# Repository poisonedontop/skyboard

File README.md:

# SkyBoard
I have been playing Hypixel Skyblock for a while now and while it's great, having keybinds to commands makes basically everything much more efficient. The problem with my normal keyboard is that it's too cluttered to set all command keybinds there as it will overlap with other keybinds.
That's why I'm creating this deck, to make a clean and efficient way to play the game. I haven't had much prior experience with electronics, so I think this will be a great first project! <br/>
Screenshot of the full case: <br/>
 <br/>

Screenshot of the schematic: <br/>

<br/>
Screenshot of the PCB:<br/>

BOM: <br/>
1x Seeed XIAO RP2040 <br/>
6x MX-Style switches <br/>
1x EC11 Rotary encoder <br/>
4x SK6812 MINI-E LEDs <br/>
3D printed case

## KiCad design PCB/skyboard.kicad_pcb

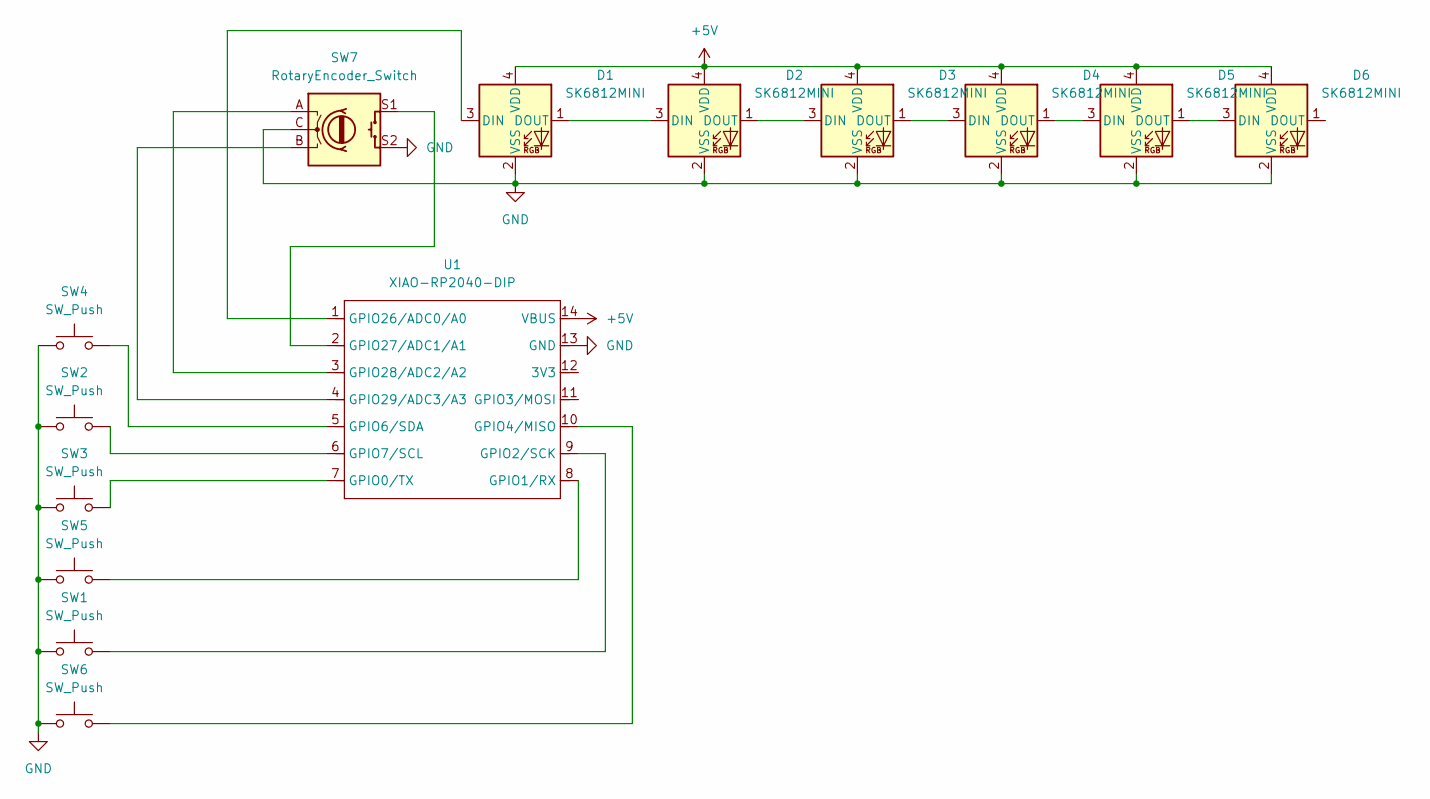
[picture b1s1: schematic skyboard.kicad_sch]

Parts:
D1, D2, D3, D4, D5, D6: SK6812MINI; MX_SK6812MINI-E_REV
SW1, SW2, SW3, SW4, SW5, SW6: SW_Push; SW_Cherry_MX_1.00u_PCB
SW7: RotaryEncoder_Switch; RotaryEncoder_Alps_EC11E-Switch_Vertical_H20mm
U1: XIAO-RP2040-DIP

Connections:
+5V: D1.4 (VDD), D2.4 (VDD), D3.4 (VDD), D4.4 (VDD), D5.4 (VDD), D6.4 (VDD), U1.14 (VBUS)
GND: D1.2 (VSS), D2.2 (VSS), D3.2 (VSS), D4.2 (VSS), D5.2 (VSS), D6.2 (VSS), SW1.1, SW2.1, SW3.1, SW4.1, SW5.1, SW6.1, SW7.C, SW7.S2, U1.13 (GND)
unnamed: D1.3 (DIN), U1.1 (GPIO26/ADC0/A0)
unnamed: D1.1 (DOUT), D2.3 (DIN)
unnamed: D2.1 (DOUT), D3.3 (DIN)
unnamed: D3.1 (DOUT), D4.3 (DIN)
unnamed: D4.1 (DOUT), D5.3 (DIN)
unnamed: D5.1 (DOUT), D6.3 (DIN)
unnamed: SW3.2, U1.7 (GPIO0/TX)
unnamed: SW5.2, U1.8 (GPIO1/RX)
unnamed: SW1.2, U1.9 (GPIO2/SCK)
unnamed: SW6.2, U1.10 (GPIO4/MISO)
unnamed: SW4.2, U1.5 (GPIO6/SDA)
unnamed: SW2.2, U1.6 (GPIO7/SCL)
unnamed: SW7.S1, U1.2 (GPIO27/ADC1/A1)
unnamed: SW7.A, U1.3 (GPIO28/ADC2/A2)
unnamed: SW7.B, U1.4 (GPIO29/ADC3/A3)

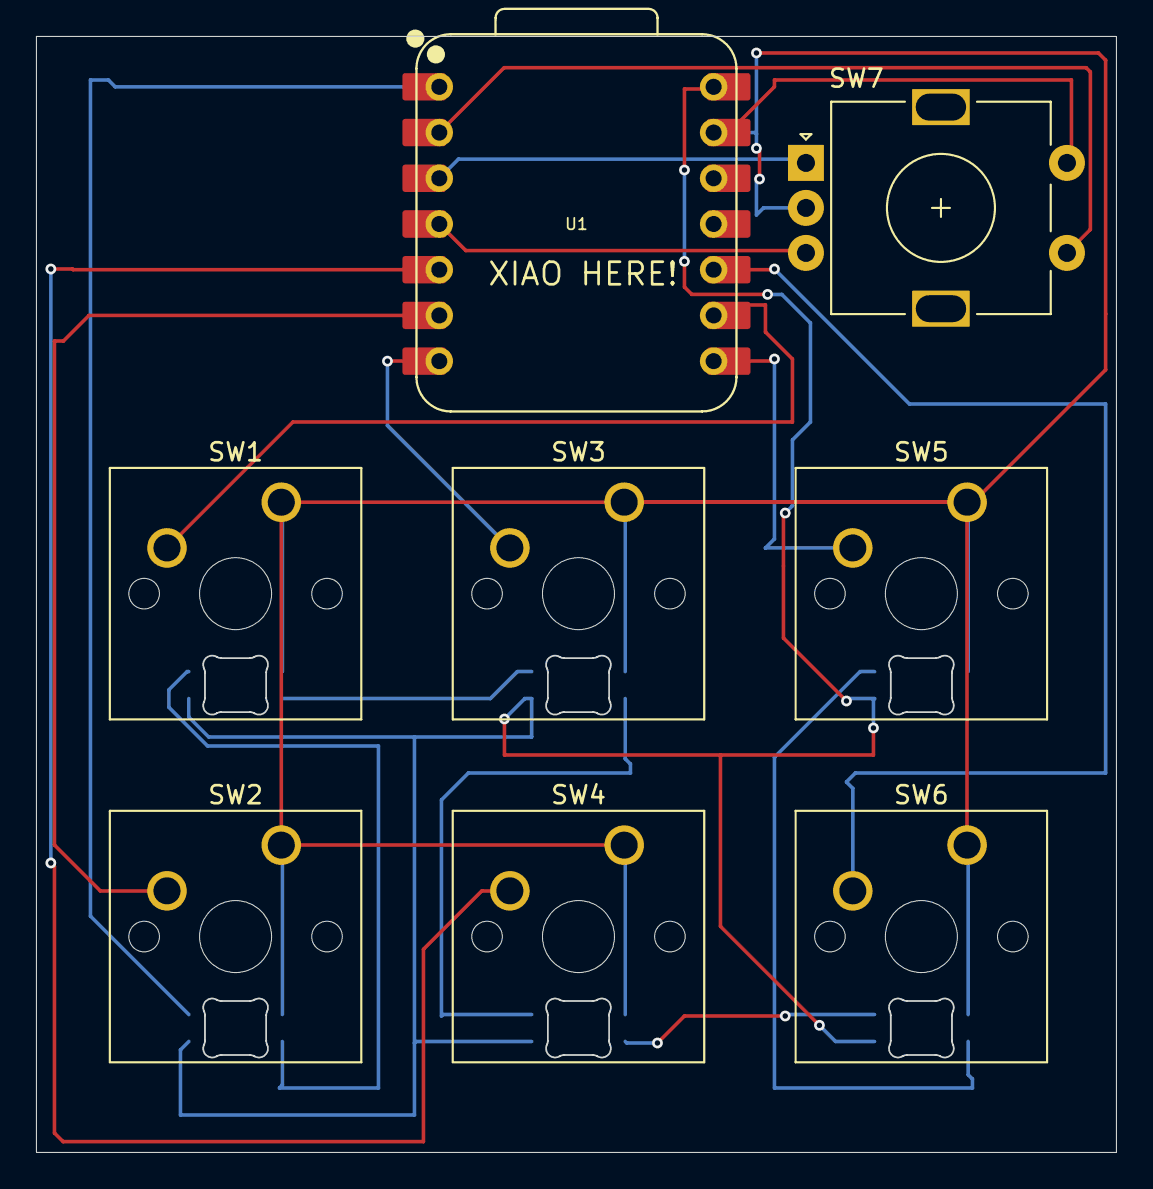
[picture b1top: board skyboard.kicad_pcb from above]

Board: 2 copper layers, 60.0 x 62.0 mm, 14 parts (0 on the bottom side), 17 nets.

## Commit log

2026-01-17 Files added
2026-01-25 Update README.md
    Added PCB to the full case picture
2026-01-25 Added ground to the LEDs
2026-01-25 Added PCB to full case picture
2026-02-21 Added extra LEDs under the switches, fixed wiring
2026-02-23 Added Fusion source files for CAD
